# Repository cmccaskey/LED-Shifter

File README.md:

# About #
Thunkit Electronics sells electronic kits for hobbyists and engineers alike. Available at [thunkitelectronics.com](https://thunkitelectronics.com) and [Tindie](https://www.tindie.com/stores/cmccaskey). All designs are open source with schematics, board layouts, code, and BOMs freely available.

## Description ###
 <br />
The LED Shifter is a useful tool for SPI debugging without the use of an oscilloscope. This board is to be wired into MOSI or MISO and SCK and will display on the 8 LEDs on the front what data is being transferred on that line. With a few delay statements in your program, it is possible to slow the SPI transfers down slow enough that you can visually see what's happening. Since this board does not require a chip select, a single board can be used to monitor MOSI or MISO on your project without requiring a board for each connected device. Additionally, this board can be used in your project if you need a simple 8-bit bar graph to use as an indicator.

## Device ##
This board is based around the 74HC624 shift register. Because of this, this board can be used to debug logic levels ranging from 2 to 6V. Red LEDs allow the board to function down to 2V because of their low forward voltage. Note: the male headers do not come pre-soldered to the board.

## Schematic ##
 <br />

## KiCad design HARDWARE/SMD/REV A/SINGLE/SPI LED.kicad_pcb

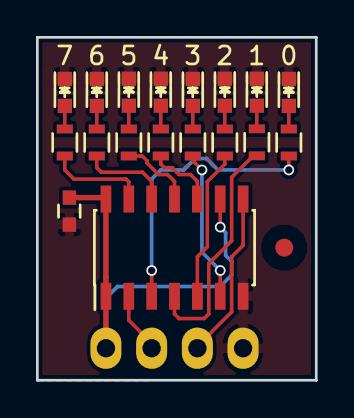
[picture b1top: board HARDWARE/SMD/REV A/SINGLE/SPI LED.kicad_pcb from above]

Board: 2 copper layers, 15.5 x 19.0 mm, 19 parts (0 on the bottom side), 20 nets.

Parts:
C1: 1uF; C_0603
D1, D2, D3, D4, D5, D6, D7, D8: RED; LED_0603
P1: CONN_01X04; Pin_Header_Straight_1x04_No_Silk_Long_Pads
R1, R2, R3, R4, R5, R6, R7, R8: 680; R_0603
U1: 74HC164; SOIC-14_3.9x8.7mm_Pitch1.27mm

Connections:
CLK: P1.3, U1.8
DATA: P1.2, U1.2
GND: C1.1, D1.1, D2.1, D3.1, D4.1, D5.1, D6.1, D7.1, D8.1, P1.4, U1.7
unnamed: D1.2, R1.2
unnamed: D2.2, R2.2
unnamed: D3.2, R3.2
unnamed: D4.2, R4.2
unnamed: D5.2, R5.2
unnamed: D6.2, R6.2
unnamed: D7.2, R7.2
unnamed: D8.2, R8.2
unnamed: R1.1, U1.13
unnamed: R2.1, U1.12
unnamed: R3.1, U1.11
unnamed: R4.1, U1.10
unnamed: R5.1, U1.6
unnamed: R6.1, U1.5
unnamed: R7.1, U1.4
unnamed: R8.1, U1.3
VCC: C1.2, P1.1, U1.1, U1.9, U1.14

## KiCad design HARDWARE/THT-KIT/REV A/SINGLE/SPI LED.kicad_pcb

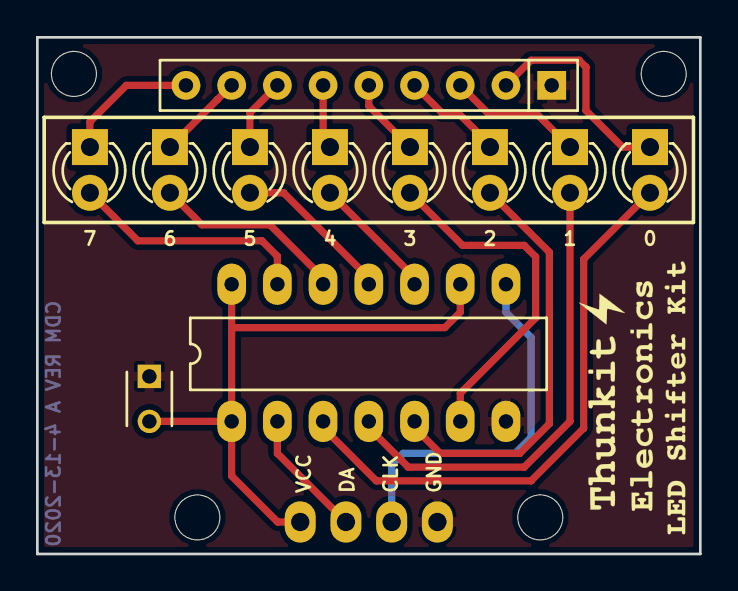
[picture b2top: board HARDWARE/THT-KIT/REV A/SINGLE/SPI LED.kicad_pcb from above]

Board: 2 copper layers, 36.8 x 28.7 mm, 12 parts (1 on the bottom side), 20 nets.

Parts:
C1: 1uF; C_Disc_D3_P2.5
D1, D2, D3, D4, D5, D6, D7, D8: RED; LED-3MM
P1: CONN_01X04; Pin_Header_Straight_1x04_No_Silk_Long_Pads
R1: 680; Resistor_Array_SIP9
U1: 74HC164; DIP-14_W7.62mm_LongPads_Dimple

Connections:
CLK: P1.3, U1.8
DATA: P1.2, U1.2
GND: C1.1, P1.4, R1.1, U1.7
unnamed: D1.1, R1.9
unnamed: D1.2, U1.13
unnamed: D2.1, R1.8
unnamed: D2.2, U1.12
unnamed: D3.1, R1.7
unnamed: D3.2, U1.11
unnamed: D4.1, R1.6
unnamed: D4.2, U1.10
unnamed: D5.1, R1.5
unnamed: D5.2, U1.6
unnamed: D6.1, R1.4
unnamed: D6.2, U1.5
unnamed: D7.1, R1.3
unnamed: D7.2, U1.4
unnamed: D8.1, R1.2
unnamed: D8.2, U1.3
VCC: C1.2, P1.1, U1.1, U1.9, U1.14

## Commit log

2020-07-11 init
2020-07-11 cleanup
2020-07-12 readme
